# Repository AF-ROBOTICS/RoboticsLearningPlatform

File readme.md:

# DFEC Robot

The DFEC Robot was created for the Department of Electrical and Computer Engineering (ECE) at the US Air Force Academy. It is used to teach ECE fundamentals in the major's introductory course. The robot's chassis is built using 3D printed parts. An Arduino Uno Rev3 microcontroller board and a custom designed power and motor controller Printed Circuit Board (PCB) are used to control the robot.

## Labs

Six labs guide the students from soldering the PCB and assembling the robot to using distance and line sensors to guide the robot through a maze.

[Robot PCB](Labs/0_robot_pcb/robot_pcb.pdf) - This lab guides students to solder and test their PCB.

[Robot Build](Labs/1_robot_build/robot_build.pdf) - This lab provides instructions to assemble the robot.

[Robot Motors](Labs/2_robot_motors/robot_motors.pdf) - This lab investigates how the Arduino uses Pulse Width Modulation to drive the robot's motors.

[Robot Drive](Labs/3_robot_drive/robot_drive.pdf) - This lab has students control the motors to drive in specified patterns.

[Robot Line Following](Labs/4_robot_linefollowing/robot_linefollowing.pdf) - This lab integrates the Pololu QTR-8RC Line Sensor Array to enable the robot to follow a black line.

[Robot Wall Following](Labs/5_robot_wallfollowing/robot_wallfollowing.pdf) - This lab integrates the Sharp GP2Y051SK0F 2-15 cm Analog Distance Sensor to enable the robot to follow walls.

[Robot Maze](Labs/6_robot_maze/robot_maze.pdf) - This lab is broken up into three parts: 1) follow a line through a maze; 2) follow a line through a maze and turn around and return to the start of the maze; and 3) navigate a walled maze towards a goal location.

## Libraries

There are two custom libraries used to control the robot. These libraries should be copied into library folder at `root/Documents/Arduino/libraries`.

[Motor](Labs/libraries/Motor/Motor.h) - This library provides functions to drive the robot using left and right PWM values (e.g., `Motor_Init()`, `Motor_Forward(int leftDuty, int rightDuty)`, and `Motor_Stop()`)

[QTR-8RC](Labs/libraries/QTR-8RC/QTR-8RC.h) - This library is adapted from the QTRSensors library to utilize the QTR-8RC Reflectance Sensor Array to determine how far the robot is off a line.

## Projects

There are several projects that incorporate the DFEC Robot into different systems. All of these are works in progress and need to be updated to utilize the new libraries.

## Hardware

### 3D Printed Chassis

Frame developed using [AutoDesk Fusion 360](https://www.autodesk.com/products/fusion-360/overview) and printed on a LulzBot Taz 6.

#### [Base layer](3D_Printing/stl/BaseLayer1.stl)

|                          Top                           |                          Bottom                           |
| :----------------------------------------------------: | :-------------------------------------------------------: |
|  |  |

#### [Motor layer](3D_Printing/stl/MotorLayer1.stl)

|                          Top                           |                          Bottom                           |
| :----------------------------------------------------: | :-------------------------------------------------------: |
|  |  |

#### [Arduino layer](3D_Printing/stl/ArduinoLayer.stl)

|                          Top                          |                           Bottom                            |
| :---------------------------------------------------: | :---------------------------------------------------------: |
|  |  |

#### [Additional Layer](3D_Printing/stl/Layer.stl)

|                      Top                       |                        Bottom                        |
| :--------------------------------------------: | :--------------------------------------------------: |
|  |  |

#### Wheels

|        [Rims](3D_Printing/stl/rim.STL)         | [Tires](3D_Printing/stl/Ninja_Flex_Tire_left.STL) |
| :--------------------------------------------: | :-----------------------------------------------: |
|  |     |

### Printed Circuit Board (PCB)

|                                                   |                                               |
| :-----------------------------------------------: | :-------------------------------------------: |
|  |  |

### [Motor](https://www.adafruit.com/product/3777)

### [Sharp GP2Y0A51SK0F Analog Distance Sensor 2-15 cm](https://www.pololu.com/product/2450)

### [QTR-8RC Reflectance Sensor Array](https://www.pololu.com/product/961)

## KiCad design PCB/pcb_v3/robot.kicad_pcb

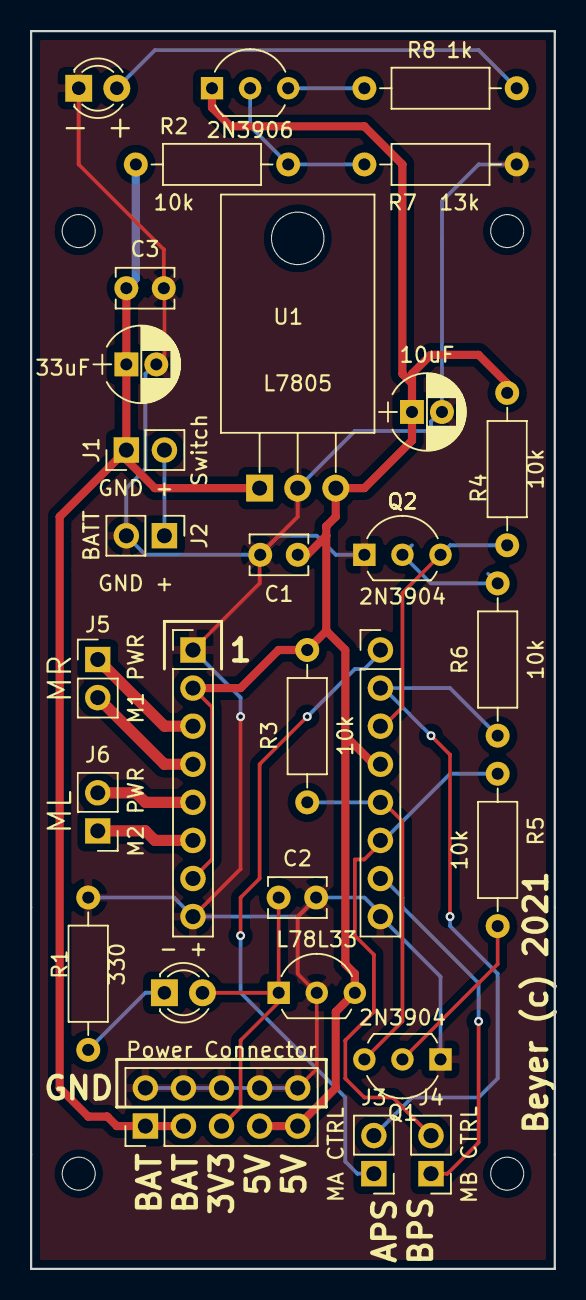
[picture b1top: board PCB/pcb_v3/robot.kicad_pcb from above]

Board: 2 copper layers, 34.9 x 82.5 mm, 28 parts (0 on the bottom side), 21 nets.

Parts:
- +: +; LED_D3.0mm
C1, C2, C3: 0.1uF; C_Disc_D3.8mm_W2.6mm_P2.50mm
C3#2: 10uF; CP_Radial_D5.0mm_P2.00mm
C6: 33uF; CP_Radial_D5.0mm_P2.00mm
D2: - +; LED_D3.0mm
J1: Switch; Pin_Header_Straight_1x02_Pitch2.54mm
J2: BATT; Pin_Header_Straight_1x02_Pitch2.54mm
J3: MA CTRL; Pin_Header_Straight_1x02_Pitch2.54mm
J3#2: Power Connector; Pin_Header_Straight_2x05_Pitch2.54mm
J4: MB CTRL; Pin_Header_Straight_1x02_Pitch2.54mm
J5: M1 PWR; Pin_Header_Straight_1x02_Pitch2.54mm
J6: M2 PWR; Pin_Header_Straight_1x02_Pitch2.54mm
J8: TB6612_Motor_Driver; Pololu_TB6612
L78L33: L78L33_TO92; TO-92L_Inline_Wide
Q1, Q2: 2N3904; TO-92L_Inline_Wide
Q3: 2N3906; TO-92_Inline_Wide
R1: 330; R_Axial_DIN0207_L6.3mm_D2.5mm_P10.16mm_Horizontal
R2, R3, R4, R5, R6: 10k; R_Axial_DIN0207_L6.3mm_D2.5mm_P10.16mm_Horizontal
R7: 13k; R_Axial_DIN0207_L6.3mm_D2.5mm_P10.16mm_Horizontal
R8: 1k; R_Axial_DIN0207_L6.3mm_D2.5mm_P10.16mm_Horizontal
U1: L7805; TO-220-3_Horizontal

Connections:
+3V3: - +.2, C2.1, J3#2.5, L78L33.1
+5V: C1.1, C3#2.1, J3#2.7, J3#2.9, J8.2, J8.7, J8.13, L78L33.3, Q3.1, R3.2, R4.2, U1.3
+BATT: C3.1, C6.1, J1.1, J3#2.1, J3#2.3, R2.1, U1.1
A1: J8.14, Q2.3, R4.1
A2: J3.2, J8.15, R6.1
APWM: J3.1, J8.16
B1: J8.12, Q1.3, R3.1
B2: J4.2, J8.11, R5.1
BPWM: J4.1, J8.10
GND: C1.2, C2.2, C3.2, C3#2.2, C6.2, D2.1, J2.2, J3#2.2, J3#2.4, J3#2.6, J3#2.8, J3#2.10, J8.1, J8.8, J8.9, L78L33.2, Q1.1, Q2.1, R1.2, R7.2, U1.2
unnamed: - +.1, R1.1
unnamed: D2.2, R8.2
unnamed: J5.1, J8.3
unnamed: J5.2, J8.4
unnamed: J6.1, J8.6
unnamed: J6.2, J8.5
unnamed: J1.2, J2.1
unnamed: Q1.2, R5.2
unnamed: Q2.2, R6.2
unnamed: Q3.2, R2.2, R7.1
unnamed: Q3.3, R8.1

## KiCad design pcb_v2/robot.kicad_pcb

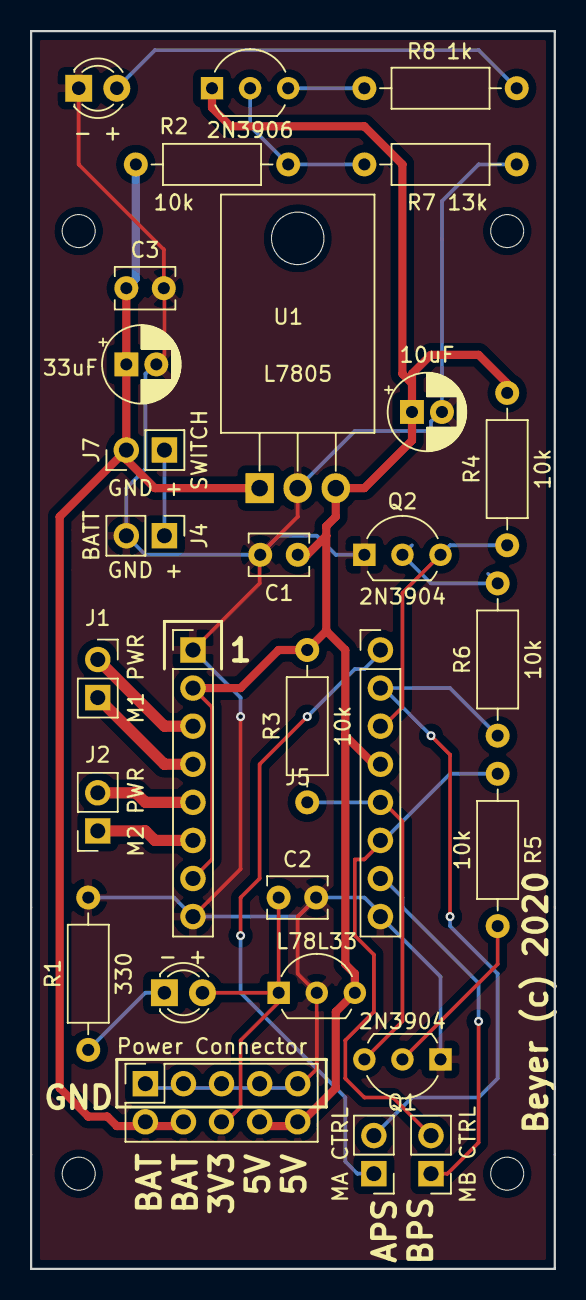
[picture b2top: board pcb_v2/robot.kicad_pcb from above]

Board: 2 copper layers, 34.9 x 82.5 mm, 28 parts (0 on the bottom side), 18 nets.

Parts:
C1, C2, C3: 0.1uF; C_Disc_D3.8mm_W2.6mm_P2.50mm
C4: 10uF; CP_Radial_D5.0mm_P2.00mm
C5: 33uF; CP_Radial_D5.0mm_P2.00mm
D1, D2: - +; LED_D3.0mm
J1: M1 PWR; PinSocket_1x02_P2.54mm_Vertical
J2: M2 PWR; PinSocket_1x02_P2.54mm_Vertical
J3: Power Connector; PinSocket_2x05_P2.54mm_Vertical
J4: BATT; PinHeader_1x02_P2.54mm_Vertical
J5: TB6612_Motor_Driver; Pololu_TB6612
J7: SWITCH; PinHeader_1x02_P2.54mm_Vertical
J11: MB CTRL; PinHeader_1x02_P2.54mm_Vertical
J12: MA CTRL; PinHeader_1x02_P2.54mm_Vertical
Q1, Q2: 2N3904; TO-92L_Inline_Wide
Q3: 2N3906; TO-92_Inline_Wide
R1: 330; R_Axial_DIN0207_L6.3mm_D2.5mm_P10.16mm_Horizontal
R2, R3, R4, R5, R6: 10k; R_Axial_DIN0207_L6.3mm_D2.5mm_P10.16mm_Horizontal
R7: 13k; R_Axial_DIN0207_L6.3mm_D2.5mm_P10.16mm_Horizontal
R8: 1k; R_Axial_DIN0207_L6.3mm_D2.5mm_P10.16mm_Horizontal
U1: L7805; TO-220-3_Horizontal_TabDown
U3: L78L33; TO-92L_Inline_Wide

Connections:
+3V3: C2.1, D1.2, J3.5, U3.1
+5V: C1.1, C4.1, J3.7, J3.9, J5.2, J5.7, J5.13, Q3.1, R3.2, R4.2, U1.3, U3.3
+BATT: C3.1, C5.1, J3.1, J3.3, J7.1, U1.1
A1: J5.14, Q2.3, R4.1
A2: J5.15, J12.2, R6.1
APWM: J5.16, J12.1
B1: J5.12, Q1.3, R3.1
B2: J5.11, J11.2, R5.1
BPWM: J5.10, J11.1
GND: C1.2, C2.2, C3.2, C4.2, C5.2, D2.1, J3.2, J3.4, J3.6, J3.8, J3.10, J4.2, J5.1, J5.8, J5.9, Q1.1, Q2.1, R1.2, U1.2, U3.2
unnamed: D1.1, R1.1
unnamed: J1.1, J5.3
unnamed: J1.2, J5.4
unnamed: J2.1, J5.6
unnamed: J2.2, J5.5
unnamed: J4.1, J7.2
unnamed: Q1.2, R5.2
unnamed: Q2.2, R6.2

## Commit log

2019-01-10 SMB, 10 Jan 19, First Commit.
2019-01-10 SMB, 10 Jan 19, Added gcode for Lulzbot.
2019-01-11 SMB, 11 Jan 19, Updated gcode to include line-following stl.
2019-01-11 SMB, 11 Jan 19, Fixed pi gcode.
2019-01-15 SMB, 15 Jan 19, testing git ignore.
2019-01-15 SMB, 15 Jan 19, still testing git ignore.
2019-01-17 SMB, 17 Jan 2019, Updated fusion files for new stacking order and changed gcode.
2019-01-18 added edge detection using line sensors.
2019-02-01 SMB, 1 Feb 2019, Created basic robot code in robot2.
2019-02-05 SMB, 5 Feb 2019, Updated wire diagrams, added some basic code, and added code for servo.
2019-02-05 SMB, 5 Feb 19, Updated baselayer and pimount.
2019-02-05 SMB, 5 Feb 19, Updated Arduino and Motor Layers .
2019-02-05 SMB, 5 Feb 19, Updated 3D print files and gcode.
2019-02-06 SMB, 6 Feb 2019, Added letters to 3d printed components.
2019-02-06 SMB, 6 Feb 19, Updated robot_camera.ino code to reset camera and increase speed of right motor.
2019-02-08 SMB, 8 Feb 2019, Added nameplate.
2019-02-19 SMB, 19 Feb 19, Added slides for arduino lesson.
2019-02-25 SMB, 25 Feb 19, Added images to camera code.
2019-02-25 SMB, 25 Feb 19, Created a basic schematic for robot wiring.
2019-02-25 SMB, 25 Feb 19, Updated folders to be a bit more clear.
2019-02-28 SMB, 28 Feb 19, updated motor layer 3d model.
2019-02-28 SMB, 28 Feb 19, Updated basic circuit fritz.
2019-03-01 SMB, 1 Mar 19, Updated gyro code with link to NXP Precision 9DoF Breakout example.
2019-03-05 SMB, 5 Mar 19, Updated 3d printing files.
2019-03-06 SMB, 6 Mar 2019, Updated motorLayer 3d print and created PCB_test code for simple testing.
2019-03-06 SMB, 6 Mar 19, Updated PCB_test code.
2019-03-06 SMB, 6 Mar 2019, Added basic drive code.
2019-03-06 SMB, 6 Mar 2019, updated basic robot_drive file.
2019-03-06 SMB, 6 Mar 19, Updated PCB test to simplify and add comments.
2019-03-07 SMB, 7 Mar 2019, Updated 3d printing gcode.
2019-03-07 SMB, 7 Mar 2019, Updated robot_drive code for basic drive lab.
2019-03-07 SMB, 7 Mar 2019, added lab write ups to the repo.
2019-03-07 SMB, 7 Mar 2019, Deleted and cleaned up some files.
2019-03-08 SMB, 8 Mar 19, Completed line following lab.
2019-03-13 SMB, 12 Mar 19, updated 3d printing files and ir sensor code.
2019-03-16 SMB, 16 Mar 19, Finished Obstacle Avoidance lap.
2019-03-16 SMB, 16 Mar 2019, Fixed some typos in line following/obstacle avoidance.
2019-04-29 SMB, solution for line following added.
2019-06-05 SMB, 5 Jun 19, updated motor layer. git push
2019-06-05 SMB, 5 Jun 19, added Fusion file for MotorLayer v2.
2019-06-10 SMB, 10 Jun 19, Updated 3d print for base.
2019-06-10 SMB, 10 Jun 19, added launchpad stands.
2019-08-07 Updated notes and robot_camera ino.
2019-08-07 SMB, 7 Aug 19, Updated 3d print files and included tachometer version of BeyerBot within Carson folder.
2019-08-29 Updated 3d print models for version 2.
2019-09-16 SMB, 16 Sep 19, Updated prints.
2019-12-10 SMB, 10 Dec 19, updated 3d print files.
2019-12-10 SMB, 10 Dec 19, Updated 3D Print for 8 Line Sensor Array. Updated drive code to create Motor.h allowing for individual control of motors. Closer code to TI Bot.
2019-12-16 SMB, 16 Dec 19, Updated solution code for line following to use a proportional controller.
2019-12-16 SMB, 16 Dec 19, updated obstacle avoidance solution to create a porportional controller that drives straight down the middle of two walls using filtered IR sensor values.
2020-02-05 Updated PCB files and some code.
2020-02-05 SMB, 5 Feb 2020, Updated code and 3d print files.
2020-02-13 SMB, 13 Feb 2020, Updated STL for Base Layer for smaller standoffs.
2020-02-13 SMB, 13 Feb 2020, Updated stl and gcode for all of the prints.
2020-02-13 SMB, 13 Feb 2020, updated BaseLayer fusion code.
2020-02-14 SMB, 14 Feb 2020, Updated gcode for latest version of 3D models.
2020-03-16 SMB, 16 Mar 2020, Added lab for motors.
2020-04-02 SMB, 2 Apr 2020, Updated build bot lab document.
2020-04-17 SMB, 17 Apr 2020, Updated PLA base layer gcode.
2020-04-17 SMB, 17 Apr 2020, Updated code for Motor.h and labs 0, 1, 2, 3.
2020-04-17 SMB, 17 Apr 2020, Updated file names.
2020-04-20 SMB, 20 Apr 20, Updated filenames in lab documents.
2020-04-22 SMB, 22 Apr 2020, updated wall following code.
2020-04-23 SMB, 23 Apr 2020, Completed line following using the QTR-8RC sensor array. Edited library, QTRSensors, to measure distance from line and saved as QTR-8RC library.
2020-04-23 SMB, 23 Apr 2020, Completed the line following lab.
2020-04-24 SMB, 24 Apr 2020, Added code to complete the maze.
2020-04-27 SMB, 27 Apr 2020, Completed lab 1 writeup.
2020-04-27 Update.
2020-04-28 Syncing repositories.
2020-04-28 sync.
2020-04-28 Added led pwm to motor lab to demonstrate PWM in different form.
2020-04-28 Printed ne pics for pcb_v2
2020-04-28 SMB, 28 Apr 2020, Updated PCB v2.
2020-04-28 SMB, 28 Apr 2020, Created PCBv3.
2020-04-28 SMB, 28 Apr 2020, Updated with PCB.
2020-04-28 SMB, updated.
2020-04-28 SMB, 28 Apr 2020, fixed error in PCB.
2020-04-29 SMB, got pictures ready for Lab 0.
2020-04-29 SMB, 28 Apr 2020, added pics to repository.
2020-04-29 SMB, 29 Apr 2020, Created v3 of 3d models.
2020-04-29 SMB, 29 Apr 2020, Updated a few things in PCB .
2020-04-29 Small changes to PCB file.
2020-04-29 SMB, 29 Apr 2020, Updated gerbers for PCB.
2020-04-29 Same
2020-04-30 SMB, PCB
2020-04-30 SMB, 30 Apr 2020, updated purchase list.
2020-05-01 SMB, 1 May 2020, Completed PCB Lab write-up.
2020-05-01 SMB, 1 May 2020, Readme.
2020-05-04 SMB, 4 May 2020, Completed Readme.
2020-05-04 Fixed picture.
2020-05-04 Edited md.
2020-05-04 SMB, 4 May 2020, Updated readme. Created file for maze project.
2020-05-04 SMB, 4 May 2020, Updated final project for maze.
2020-07-31 SMB, 31 Jul 2020, Updated PCB files.
2020-07-31 SMB, 31 Jul 2020, Pics
2020-08-12 SMB, 11 Aug 2020, Updated lab format to include DFEC badge.
2020-08-17 SMB, Update.
2020-08-17 SMB, 17 Aug 2020, fix.
2020-08-26 SMB, 26 Aug 2020, Updated all layer gcode.
2020-09-02 SMB, 2 Sep 2020, fixed some issues where figures and folders in lab disappeared.
2020-09-02 SMB, 2 Sept 2020, Fixed error in Robot PCB'
2020-10-07 SMB, updated asee paper abstract.
2021-02-24 SMB, 24 Feb 2021, updated wiring schematic for PCB.
2021-02-24 SMB, 24 Feb 2021, updated kicad files.
2021-04-06 SMB, updated labs.
2021-05-01 SMB, 1 May 2021, Removed ASEE.
2021-06-30 Updates parts inventory and parts needed for AY2021-2022
2021-07-27 SMB, 27 Jul 2021, Added ASEE documents.
2021-09-28 Adds gcode file for printing 8 rims at a time
2022-01-28 Moved old .stls to archive folder.

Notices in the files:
PCB/pcb_v3/robot.kicad_pcb:
Beyer (c) 2021
pcb_v2/robot.kicad_pcb:
Beyer (c) 2020
